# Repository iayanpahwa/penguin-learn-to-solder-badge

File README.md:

# Learn to Solder Badge 

-------------------------------------
This project is Certified with [OSHWA](https://certification.oshwa.org/in000014.html) (OSHWA UID IN000014)

## Made for beginner Soldering workshops at [India Linux User group Delhi](http://www.linuxdelhi.org) and [Hardware Hackers Club Delhi](http://hardwarehackersclub.com)

## Coming Soon : (feel free to contribute)

- Through Hole Version
- 555 Blinky version 
- SAO version

## Made With ❤ for Open Hardware using:

- [KiCad v4](http://kicad.org)
- [SVG2Shenzen Plugin](https://github.com/badgeek/svg2shenzhen)

### For best results fabricate in Black Solder Mask and White Silk Screen with ENIG-RHOS surface finish

-------------------------------------

### The PCB artwork is highly modified version of Penguin art [originally created](https://www.freepik.com/free-vector/penguin-with-gray-color_4555687.htm#page=2&query=brgfx%20penguin&position=12) by user Brgfx on Freepik to be used in free and commercial projects with proper attributions 

Attributes: Designed by Brgfx / Freepik

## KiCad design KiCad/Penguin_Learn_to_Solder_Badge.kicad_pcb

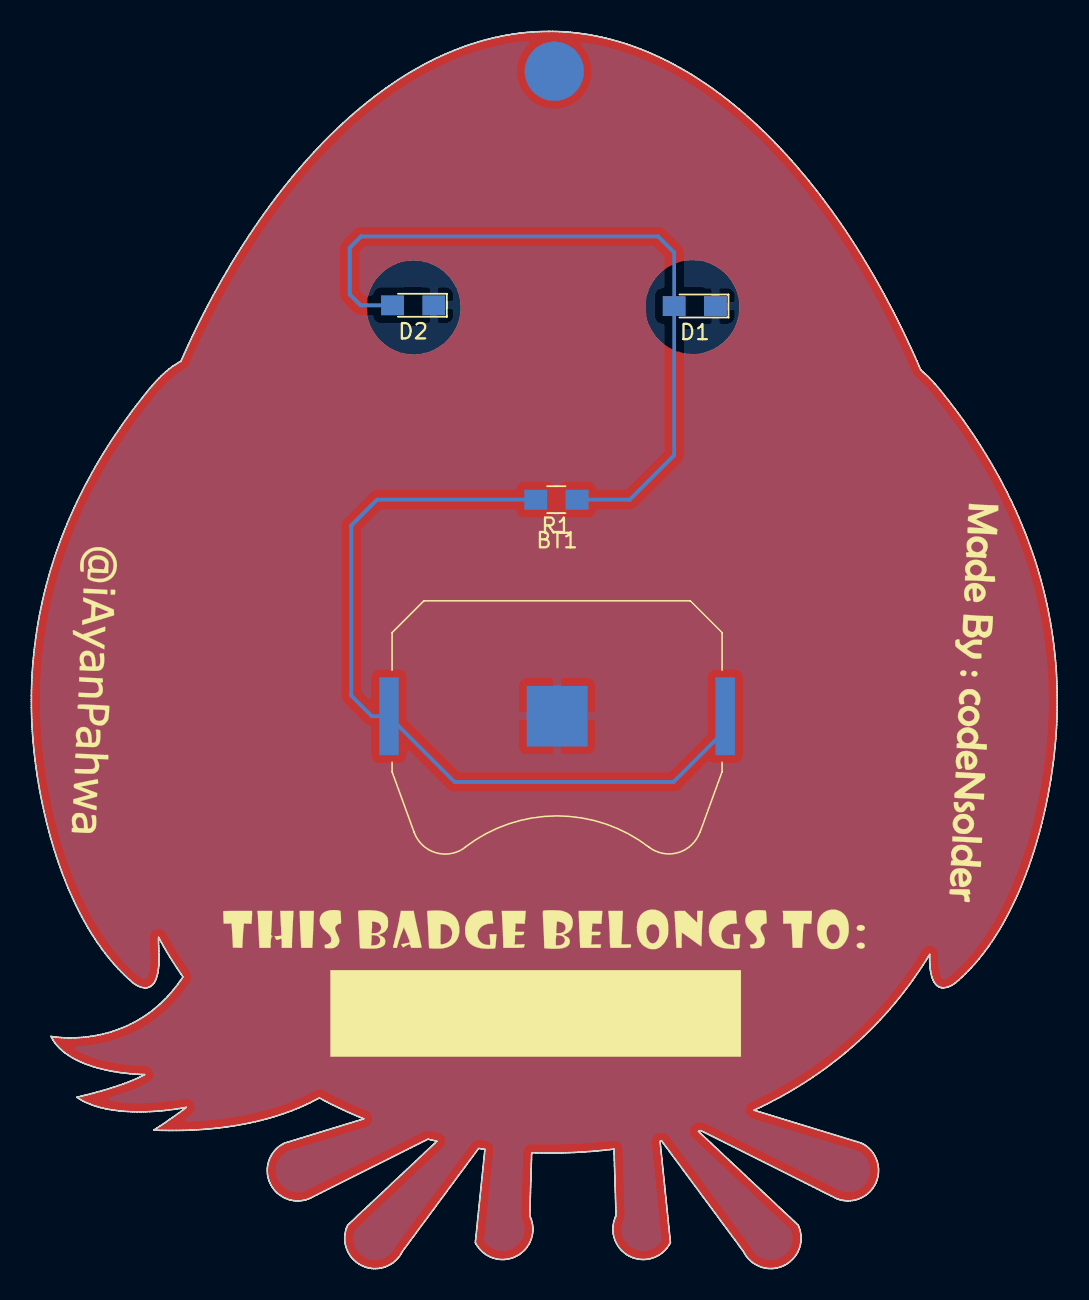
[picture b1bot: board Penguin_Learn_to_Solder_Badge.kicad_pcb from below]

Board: 2 copper layers, 67.0 x 80.8 mm, 4 parts (4 on the bottom side), 3 nets.

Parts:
BT1: 3v; Keystone_3034_1x20mm-CoinCell
D1, D2: LED; LED_0805_HandSoldering
R1: 50R; R_0805_HandSoldering

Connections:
GND: BT1.2, D1.1, D2.1
unnamed: BT1.1, R1.2
unnamed: D1.2, D2.2, R1.1

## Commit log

2020-05-01 Design files
2020-05-01 Fixed readme
2020-05-01 Fixed link in readme
2020-05-01 SAO version directory
2020-05-13 Added oshwa certification number
2021-11-09 Update README.md
    https://forum.kicad.info/t/warning-avoid-all-links-to-kicad-pcb-org-use-kicad-org/31521
